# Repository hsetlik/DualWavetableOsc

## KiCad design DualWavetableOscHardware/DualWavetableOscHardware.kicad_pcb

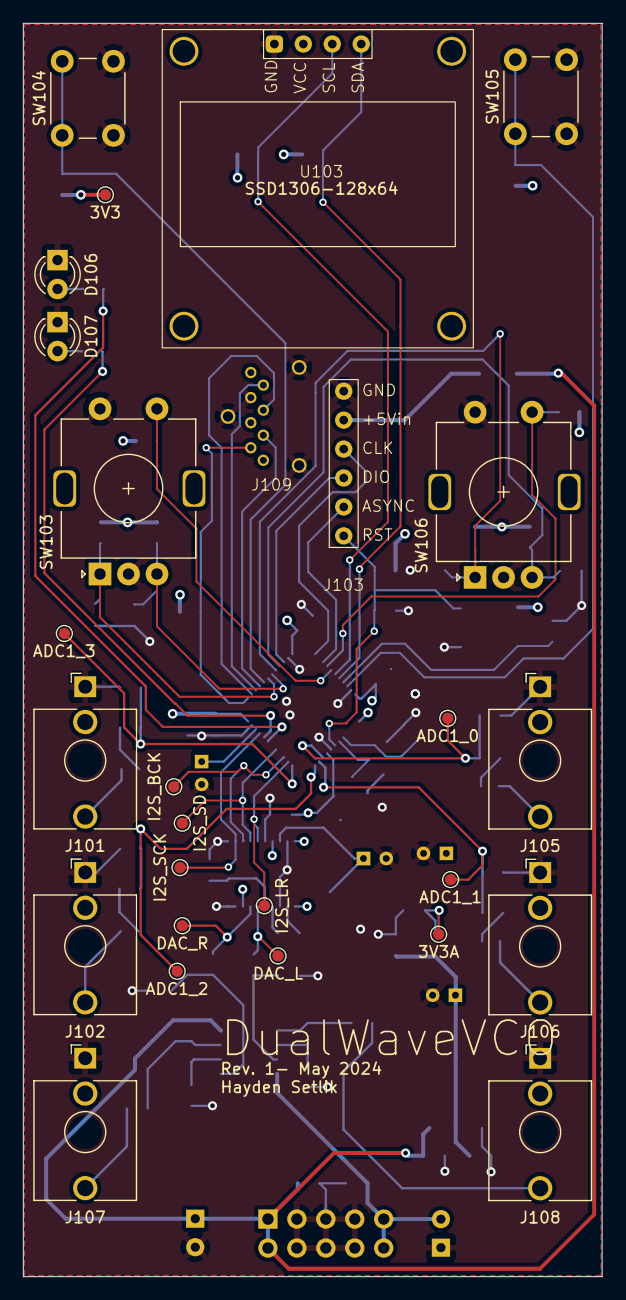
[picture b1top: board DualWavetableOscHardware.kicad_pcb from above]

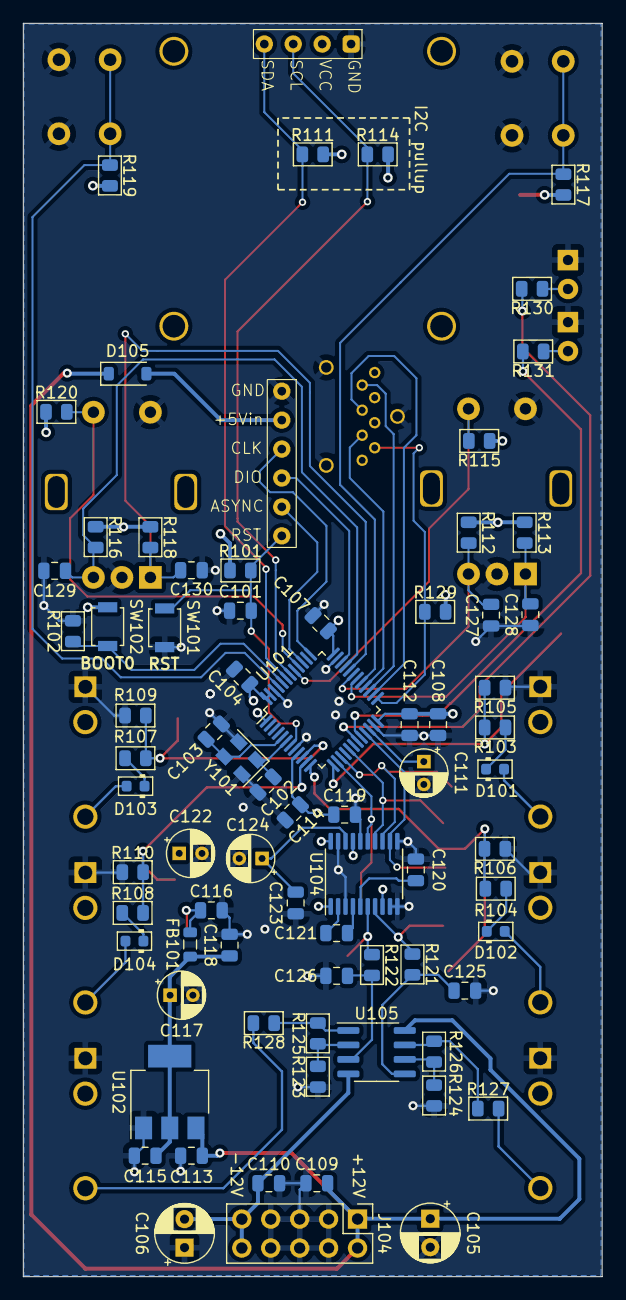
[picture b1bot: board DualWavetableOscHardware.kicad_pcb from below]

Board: 4 copper layers, 50.8 x 110.0 mm, 102 parts (75 on the bottom side), 62 nets.

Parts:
C101, C107, C108, C112, C113, C115, C119, C123, C127, C128, C129, C130: 100n; C_0805_2012Metric
C102, C103: 6pF; C_0805_2012Metric
C104, C116, C118: 2u2; C_0805_2012Metric
C105, C106: 10u; CP_Radial_D5.0mm_P2.50mm
C109, C110: 220n; C_0805_2012Metric
C111: 4u7; CP_Radial_D4.0mm_P2.00mm
C114: 10n; C_0805_2012Metric
C117, C122, C124: 10u; CP_Radial_D4.0mm_P2.00mm
C120, C121: 2.2u; C_0805_2012Metric
C125, C126: 2.2n; C_0805_2012Metric
D101, D102, D103, D104: D_Schottky; D_0603_1608Metric
D105: 1N4148; D_SOD-123
D106: LED_GRN; LED_D3.0mm
D107: LED_RED; LED_D3.0mm
FB101: 90R; L_0805_2012Metric
J101: CV1; Jack_3.5mm_QingPu_WQP-PJ398SM_Vertical_CircularHoles
J102: MOD1; Jack_3.5mm_QingPu_WQP-PJ398SM_Vertical_CircularHoles
J103: SWD Header; ST_SWHeader_3Wire_Pin
J104: POWER; PinHeader_2x05_P2.54mm_Vertical
J105: CV2; Jack_3.5mm_QingPu_WQP-PJ398SM_Vertical_CircularHoles
J106: MOD2; Jack_3.5mm_QingPu_WQP-PJ398SM_Vertical_CircularHoles
J107: OUT1; Jack_3.5mm_QingPu_WQP-PJ398SM_Vertical_CircularHoles
J108: OUT2; Jack_3.5mm_QingPu_WQP-PJ398SM_Vertical_CircularHoles
J109: Micro_SD_Card; microSD_Genesis_Vertical_THT
R101: 47k; R_0805_2012Metric
R102, R112, R113, R115, R116, R117, R118, R119, R120, R129: 10k; R_0805_2012Metric
R103, R104, R107, R108, R123, R124: 100k; R_0805_2012Metric
R105, R106, R109, R110: 33k; R_0805_2012Metric
R111, R114: R_PULLUP; R_0805_2012Metric
R121, R122, R127, R128: 470; R_0805_2012Metric
R125, R126: 68k; R_0805_2012Metric
R130, R131: 220; R_0805_2012Metric
SW101: RST; SW_SPST_B3U-1000P
SW102: BOOT; SW_SPST_B3U-1000P
SW103: ENC1; RotaryEncoder_Alps_EC11E-Switch_Vertical_H20mm_5Pin
SW104: CH; SW_PUSH_6mm
SW105: MODE; SW_PUSH_6mm
SW106: ENC2; RotaryEncoder_Alps_EC11E-Switch_Vertical_H20mm_5Pin
TP101: I2S_SCK; TestPoint_Pad_D1.0mm_Value
TP102: I2S_BCK; TestPoint_Pad_D1.0mm_Value
TP103: 3V3A; TestPoint_Pad_D1.0mm_Value
TP104: 3V3; TestPoint_Pad_D1.0mm_Value
TP105: DAC_R; TestPoint_Pad_D1.0mm_Value
TP106: DAC_L; TestPoint_Pad_D1.0mm_Value
TP107: ADC1_0; TestPoint_Pad_D1.0mm_Value
TP108: ADC1_1; TestPoint_Pad_D1.0mm_Value
TP109: I2S_SD; TestPoint_Pad_D1.0mm_Value
TP110: I2S_LR; TestPoint_Pad_D1.0mm_Value
TP111: ADC1_2; TestPoint_Pad_D1.0mm_Value
TP112: ADC1_3; TestPoint_Pad_D1.0mm_Value
U101: STM32F410CBTx; LQFP-48_7x7mm_P0.5mm
U102: AMS1117; SOT-223-3_TabPin2
U103: SSD1306-128x64; SSD1306_OLED_128x64
U104: PCM5100A; TSSOP-20_4.4x6.5mm_P0.65mm
U105: TL072; SOIC-8_3.9x4.9mm_P1.27mm
Y101: 16MHz; Crystal_SMD_EuroQuartz_MT-4Pin_3.2x2.5mm

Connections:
+3.3V: C104.1, C107.1, C108.1, C112.1, C115.2, C117.1, C118.1, FB101.1, J109.4 (VDD), R101.1, R111.2, R112.1, R113.1, R114.2, R115.1, R116.1, R117.2, R118.1, R119.2, R120.1, R129.2, SW102.1 (A), TP104.1, U101.1 (VBAT), U101.24 (VDD), U101.36 (VDD), U101.47 (PDR_ON), U101.48 (VDD), U102.2 (VO), U103.2 (VCC)
+3.3VA: C114.1, C116.1, C119.1, C122.1, FB101.2, TP103.1, U101.9 (VDDA), U104.1 (CPVDD), U104.8 (AVDD), U104.17 (XSMT), U104.20 (DVDD)
+12V: C105.1, C109.2, C113.2, D105.1 (K), J104.1, J104.2, U102.3 (VI), U105.8 (V+)
-12V: C106.2, C110.1, J104.9, J104.10, U105.4 (V-)
BOOT0: R102.1, SW102.2 (B), U101.44 (BOOT0)
CH_BTN: R117.1, SW104.1 (A), U101.29 (PA8)
CV1: D101.2 (A), J101.T
CV1_ADC: R103.2, R105.2, TP112.1, U101.13 (PA3)
CV2: D103.2 (A), J105.T
CV2_ADC: R107.2, R109.2, TP107.1, U101.10 (PA0)
ENC1_B: R115.2, SW103.S1, U101.41 (PB5)
ENC1_L: C128.2, R113.2, SW103.A, U101.30 (PA9)
ENC1_R: C127.2, R112.2, SW103.B, U101.31 (PA10)
ENC2_B: R120.2, SW106.S1, U101.40 (PB4)
ENC2_L: C130.2, R118.2, SW106.A, U101.32 (PA11)
ENC2_R: C129.2, R116.2, SW106.B, U101.33 (PA12)
GND: C101.1, C102.1, C103.1, C104.2, C105.2, C106.1, C107.2, C108.2, C109.1, C110.2, C111.2, C112.2, C113.1, C114.2, C115.1, C116.2, C117.2, C118.2, C119.2, C120.2, C122.2, C123.2, C124.2, C125.2, C126.2, C127.1, C128.1, C129.1, C130.1, D106.1 (K), D107.1 (K), J101.S, J102.S, J103.1 (GND), J104.3, J104.4, J104.5, J104.6, J104.7, J104.8, J105.S, J106.S, J107.S, J108.S, J109.6 (VSS), J109.9 (SHIELD), R102.2, R105.1, R106.1, R109.1, R110.1, R123.1, R124.1, SW101.2 (B), SW103.C, SW103.S2, SW104.2 (B), SW105.2 (B), SW106.C, SW106.S2, U101.8 (VSSA), U101.23 (VSS), U101.35 (VSS), U101.46 (VSS), U102.1 (ADJ), U103.1 (GND), U104.3 (CPGND), U104.9 (AGND), U104.10 (DEMP), U104.11 (FLT), U104.16 (FMT), U104.19 (DGND), Y101.2, Y101.4
HSE_IN: C103.2, U101.5 (PH0), Y101.3
HSE_OUT: C102.2, U101.6 (PH1), Y101.1
I2S_BCK: TP102.1, U101.15 (PA5), U104.13 (BCK)
I2S_DIO: TP109.1, U101.17 (PA7), U104.14 (DIN)
I2S_SCK: TP101.1, U101.21 (PB10), U104.12 (SCK)
I2S_WS: TP110.1, U101.14 (PA4), U104.15 (LRCK)
LED_GRN: R130.2, U101.19 (PB1)
LED_RED: R131.2, U101.20 (PB2)
MISO: J109.7 (DAT0), U101.27 (PB14)
MOD1: D102.2 (A), J102.T
MOD1_ADC: R104.2, R106.2, TP111.1, U101.12 (PA2)
MOD2: D104.2 (A), J106.T
MOD2_ADC: R108.2, R110.2, TP108.1, U101.11 (PA1)
MODE_BTN: R119.1, SW105.1 (A), U101.45 (PB8)
MOSI: J109.3 (CMD), U101.28 (PB15)
NRST: C101.2, J103.6 (RST), R101.2, SW101.1 (A), U101.7 (NRST)
unnamed: D101.1 (K), R103.1
unnamed: D102.1 (K), R104.1
unnamed: D103.1 (K), R107.1
unnamed: D104.1 (K), R108.1
unnamed: D106.2 (A), R130.1
unnamed: D107.2 (A), R131.1
unnamed: R125.2, R128.1, U105.1
unnamed: R126.2, R127.1, U105.7
unnamed: C111.1, U101.22 (VCAP1)
unnamed: C121.2, U104.4 (CAPM)
unnamed: C121.1, U104.2 (CAPP)
unnamed: C123.1, C124.1, U104.18 (LDOO)
unnamed: R122.1, TP106.1, U104.6 (OUTL)
unnamed: R121.1, TP105.1, U104.7 (OUTR)
unnamed: C120.1, U104.5 (VNEG)
unnamed: C126.1, R122.2, U105.3 (+)
unnamed: R123.2, R125.1, U105.2 (-)
unnamed: C125.1, R121.2, U105.5 (+)
unnamed: R124.2, R126.1, U105.6 (-)
Out1: J107.T, R127.2
Out2: J108.T, R128.2
SCK: J109.5 (CLK), U101.26 (PB13)
SCL: R114.1, U101.42 (PB6), U103.3 (SCL)
SDA: R111.1, U101.43 (PB7), U103.4 (SDA)
SD_CS: J109.2 (DAT3/CD), R129.1, U101.25 (PB12)
SWCLK: J103.3 (SWCLK), U101.37 (PA14)
SWDIO: J103.4 (SWDIO), U101.34 (PA13)
SWO: J103.5 (SWO), U101.39 (PB3)
VCC_DEBUG: D105.2 (A), J103.2 (VCC)

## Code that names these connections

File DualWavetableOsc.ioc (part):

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Mcu.Name=STM32F410C(8-B)Tx
Mcu.Package=LQFP48
Mcu.UserName=STM32F410CBTx
PA0-WKUP.GPIOParameters=GPIO_Label
PA0-WKUP.GPIO_Label=CV2
PA0-WKUP.Signal=ADCx_IN0
PA1.GPIOParameters=GPIO_Label
PA1.GPIO_Label=MOD2
PA1.Signal=ADCx_IN1
PA10.GPIOParameters=GPIO_Label
PA10.GPIO_Label=ENC2_R
PA10.Signal=GPIO_Input
PA11.GPIOParameters=GPIO_Label
PA11.GPIO_Label=ENC1_L
PA11.Signal=GPIO_Input
PA12.GPIOParameters=GPIO_Label
PA12.GPIO_Label=ENC1_R
PA12.Signal=GPIO_Input
PA13.Mode=Trace_Asynchronous_SW
PA13.Signal=SYS_JTMS-SWDIO
PA14.Mode=Trace_Asynchronous_SW
PA14.Signal=SYS_JTCK-SWCLK
PA2.GPIOParameters=GPIO_Label
PA2.GPIO_Label=MOD1
PA2.Signal=ADCx_IN2
PA3.GPIOParameters=GPIO_Label
PA3.GPIO_Label=CV1
PA3.Signal=ADCx_IN3
PA4.Mode=Half_Duplex_Master
PA4.Signal=I2S1_WS
PA5.Mode=Half_Duplex_Master
PA5.Signal=I2S1_CK
PA7.Mode=Half_Duplex_Master
PA7.Signal=I2S1_SD
PA8.GPIOParameters=GPIO_Label
PA8.GPIO_Label=CH_BTN
PA8.Signal=GPIO_Input
PA9.GPIOParameters=GPIO_Label
PA9.GPIO_Label=ENC2_L
PA9.Signal=GPIO_Input
PB1.GPIOParameters=GPIO_Label
PB1.GPIO_Label=LED_GRN
PB1.Signal=GPIO_Output
PB10.Mode=Master_Clock_Activated
PB10.Signal=I2S1_MCK
PB12.GPIOParameters=GPIO_Label
PB12.GPIO_Label=SD_CS
PB12.Signal=GPIO_Input
PB13.Mode=Full_Duplex_Master
PB13.Signal=SPI2_SCK
PB14.Mode=Full_Duplex_Master
PB14.Signal=SPI2_MISO
PB15.Mode=Full_Duplex_Master
PB15.Signal=SPI2_MOSI
PB2.GPIOParameters=GPIO_Label
PB2.GPIO_Label=LED_RED
PB2.Signal=GPIO_Output
PB3.Mode=Trace_Asynchronous_SW
PB3.Signal=SYS_JTDO-SWO
PB4.GPIOParameters=GPIO_Label
PB4.GPIO_Label=ENC2_B
PB4.Signal=GPIO_Input
PB5.GPIOParameters=GPIO_Label
PB5.GPIO_Label=ENC1_B
PB5.Signal=GPIO_Input
PB6.Mode=I2C
PB6.Signal=I2C1_SCL
PB7.Mode=I2C
PB7.Signal=I2C1_SDA
PB8.GPIOParameters=GPIO_Label
PB8.GPIO_Label=MODE_BTN
PB8.Signal=GPIO_Input
PH0\ -\ OSC_IN.Mode=HSE-External-Oscillator
PH0\ -\ OSC_IN.Signal=RCC_OSC_IN
PH1\ -\ OSC_OUT.Mode=HSE-External-Oscillator
PH1\ -\ OSC_OUT.Signal=RCC_OSC_OUT
RCC.HSE_VALUE=16000000
RCC.SYSCLKFreq_VALUE=100000000
RCC.SYSCLKSource=RCC_SYSCLKSOURCE_PLLCLK
board=custom

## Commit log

2024-05-11 schematic files
2024-05-11 rough schematic
2024-05-13 pcb rev 1
2024-05-13 double buffer for I2S
2024-05-13 added OLED driver
2024-05-13 actually added OLED driver
2024-05-13 status LEDs and test points
2024-05-13 status LED code
2024-05-13 ADC stuff
2024-05-13 untracked debug oops
2024-05-14 removed junk
2024-05-14 printf debugging stuff
2024-05-14 math stuff
2024-05-14 new stackup/routing
2024-05-15 wavetable generation
2024-05-15 wavetable voice logic
